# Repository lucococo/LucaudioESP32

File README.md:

View this project on [CADLAB.io](https://cadlab.io/project/28745). 

# LucaudioESP32

_Project inspired by [sonocotta ESP audio docks.](https://github.com/sonocotta/esp32-audio-dock/tree/main)_

I wanted a solution for wireless audio multiroom synchronized players, and the best I found was projects using [squeezelite-esp32](https://github.com/sle118/squeezelite-esp32).

I did my own board because firstly I wanted to improve my cad skills, and also because I like bringing my own personnal touch.
Project is still in development, I'm adding new features on my pcb later on

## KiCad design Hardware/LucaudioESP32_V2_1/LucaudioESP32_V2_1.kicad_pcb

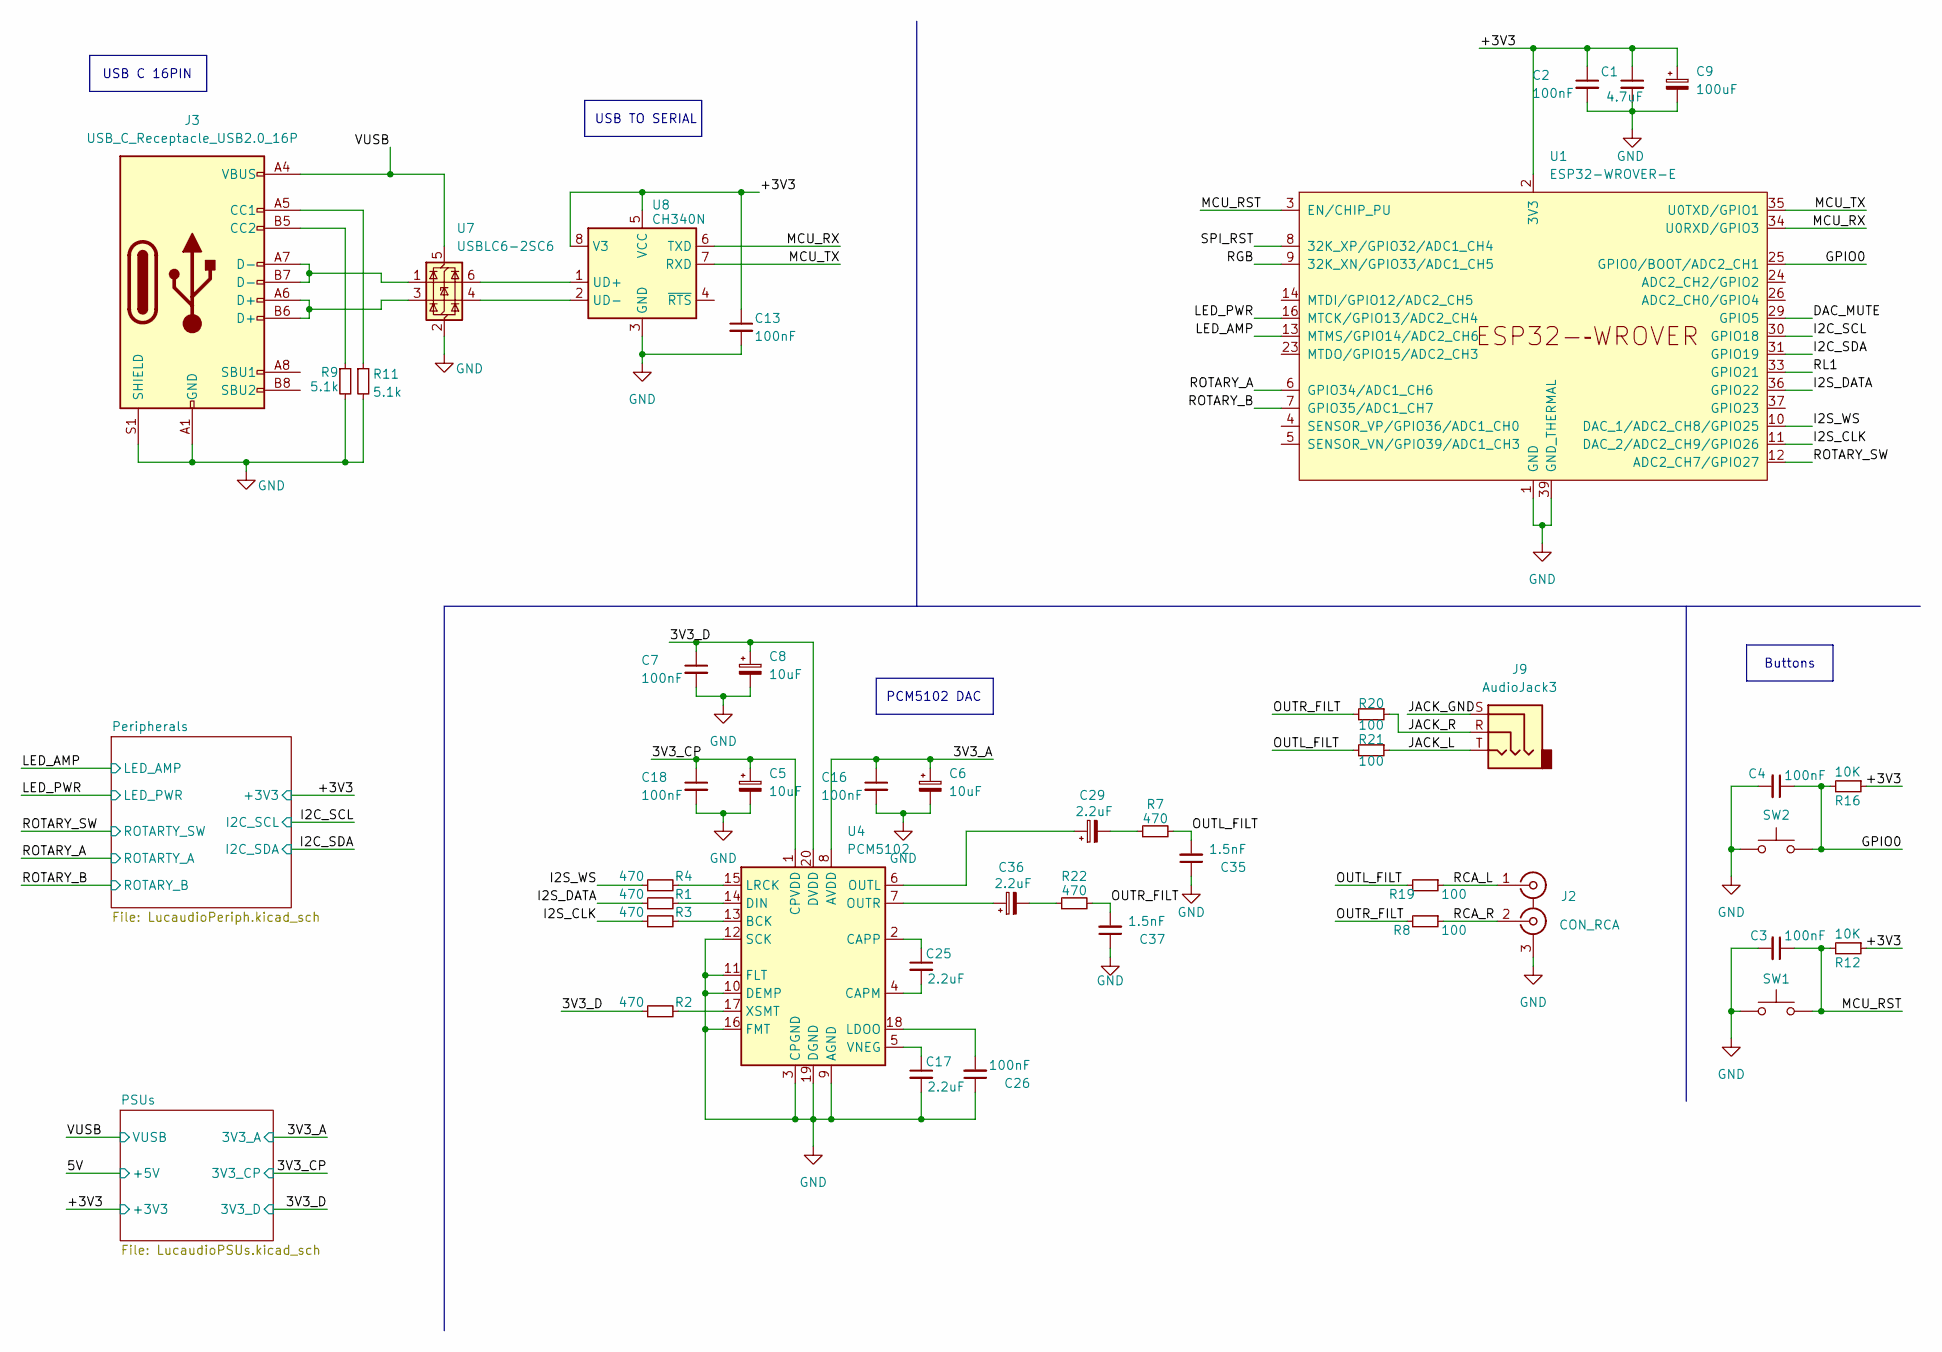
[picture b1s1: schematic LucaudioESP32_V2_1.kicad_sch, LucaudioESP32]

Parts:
C1: 4.7uF; C_0805_2012Metric_Pad1.18x1.45mm_HandSolder
C2, C7, C16, C18, C26: 100nF; C_0805_2012Metric_Pad1.18x1.45mm_HandSolder
C3, C4, C13: 100nF; C_0805_2012Metric
C5, C6, C8: 10uF; CP_Elec_5x4.5
C9: 100uF; CP_Elec_5x4.5
C17, C25: 2.2uF; C_0805_2012Metric_Pad1.18x1.45mm_HandSolder
C29, C36: 2.2uF; CP_EIA-3216-10_Kemet-I
C35, C37: 1.5nF; C_0805_2012Metric_Pad1.18x1.45mm_HandSolder
J2: CON_RCA; 2x RCA
J3: USB_C_Receptacle_USB2.0_16P; USB_C_Receptacle_G-Switch_GT-USB-7010ASV
J9: AudioJack3; JST_3p_audio
R1, R2, R3, R4, R7, R22: 470; R_0805_2012Metric_Pad1.20x1.40mm_HandSolder
R8, R19, R20, R21: 100; R_0805_2012Metric_Pad1.20x1.40mm_HandSolder
R9, R11: 5.1k; R_0805_2012Metric_Pad1.20x1.40mm_HandSolder
R12, R16: 10K; R_0805_2012Metric_Pad1.20x1.40mm_HandSolder
SW1, SW2: SW_Omron_B3FS; SW_SPST_Omron_B3FS-100xP
U1: ESP32-WROVER-E
U4: PCM5102; TSSOP-20_4.4x6.5mm_P0.65mm
U7: USBLC6-2SC6; SOT-23-6
U8: CH340N; SOP-8_3.9x4.9mm_P1.27mm

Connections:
/3V3_A: C6.1, C16.1, U4.8 (AVDD); also elsewhere on the board
/3V3_CP: C5.1, C18.1, U4.1 (CPVDD); also elsewhere on the board
/3V3_D: C7.1, C8.1, R2.1, U4.20 (DVDD); also elsewhere on the board
/+3V3: C1.1, C2.1, C9.1, C13.1, R12.1, R16.1, U1.2 (3V3), U8.5 (VCC), U8.8 (V3); also elsewhere on the board
/DAC_MUTE: U1.29 (GPIO5)
/GPIO0: C4.1, R16.2, SW2.2, U1.25 (GPIO0/BOOT/ADC2_CH1)
/I2C_SCL: U1.30 (GPIO18); also elsewhere on the board
/I2C_SDA: U1.31 (GPIO19); also elsewhere on the board
/I2S_CLK: R3.1, U1.11 (DAC_2/ADC2_CH9/GPIO26)
/I2S_DATA: R1.1, U1.36 (GPIO22)
/I2S_WS: R4.1, U1.10 (DAC_1/ADC2_CH8/GPIO25)
/JACK_GND: J9.S
/JACK_L: J9.T, R21.1
/JACK_R: J9.R, R20.1
/LED_AMP: U1.13 (MTMS/GPIO14/ADC2_CH6); also elsewhere on the board
/LED_PWR: U1.16 (MTCK/GPIO13/ADC2_CH4); also elsewhere on the board
/MCU_RST: C3.1, R12.2, SW1.2, U1.3 (EN/CHIP_PU)
/MCU_RX: U1.34 (U0RXD/GPIO3), U8.6 (TXD)
/MCU_TX: U1.35 (U0TXD/GPIO1), U8.7 (RXD)
/OUTL_FILT: C35.2, R7.2, R19.2, R21.2
/OUTR_FILT: C37.2, R8.2, R20.2, R22.2
/RCA_L: J2.1 (IN1), R19.1
/RCA_R: J2.2 (IN2), R8.1
/RGB: U1.9 (32K_XN/GPIO33/ADC1_CH5)
/RL1: U1.33 (GPIO21)
/ROTARY_A: U1.6 (GPIO34/ADC1_CH6); also elsewhere on the board
/ROTARY_B: U1.7 (GPIO35/ADC1_CH7); also elsewhere on the board
/ROTARY_SW: U1.12 (ADC2_CH7/GPIO27); also elsewhere on the board
/SPI_RST: U1.8 (32K_XP/GPIO32/ADC1_CH4)
/VUSB: J3.A4 (VBUS), J3.A9 (VBUS), J3.B4 (VBUS), J3.B9 (VBUS), U7.5 (VBUS); also elsewhere on the board
GND: C1.2, C2.2, C3.2, C4.2, C5.2, C6.2, C7.2, C8.2, C9.2, C13.2, C16.2, C17.2, C18.2, C26.1, C35.1, C37.1, J2.3 (EXT), J3.A1 (GND), J3.A12 (GND), J3.B1 (GND), J3.B12 (GND), J3.S1 (SHIELD), R9.2, R11.2, SW1.1, SW2.1, U1.1 (GND), U1.15 (GND), U1.38 (GND), U1.39 (GND_THERMAL), U4.3 (CPGND), U4.9 (AGND), U4.10 (DEMP), U4.11 (FLT), U4.12 (SCK), U4.16 (FMT), U4.19 (DGND), U7.2 (GND), U8.3 (GND); also elsewhere on the board
unnamed: C29.2, R7.1
unnamed: C36.2, R22.1
unnamed: J3.A5 (CC1), R11.1
unnamed: J3.B5 (CC2), R9.1
unnamed: J3.A6 (D+), J3.B6 (D+), U7.3 (I/O2)
unnamed: J3.A7 (D-), J3.B7 (D-), U7.1 (I/O1)
unnamed: R3.2, U4.13 (BCK)
unnamed: C25.2, U4.4 (CAPM)
unnamed: C25.1, U4.2 (CAPP)
unnamed: R1.2, U4.14 (DIN)
unnamed: C26.2, U4.18 (LDOO)
unnamed: R4.2, U4.15 (LRCK)
unnamed: C29.1, U4.6 (OUTL)
unnamed: C36.1, U4.7 (OUTR)
unnamed: C17.1, U4.5 (VNEG)
unnamed: R2.2, U4.17 (XSMT)
unnamed: U7.6 (I/O1), U8.1 (UD+)
unnamed: U7.4 (I/O2), U8.2 (UD-)

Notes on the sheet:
PCM5102 DAC
USB C 16PIN
Buttons
USB TO SERIAL

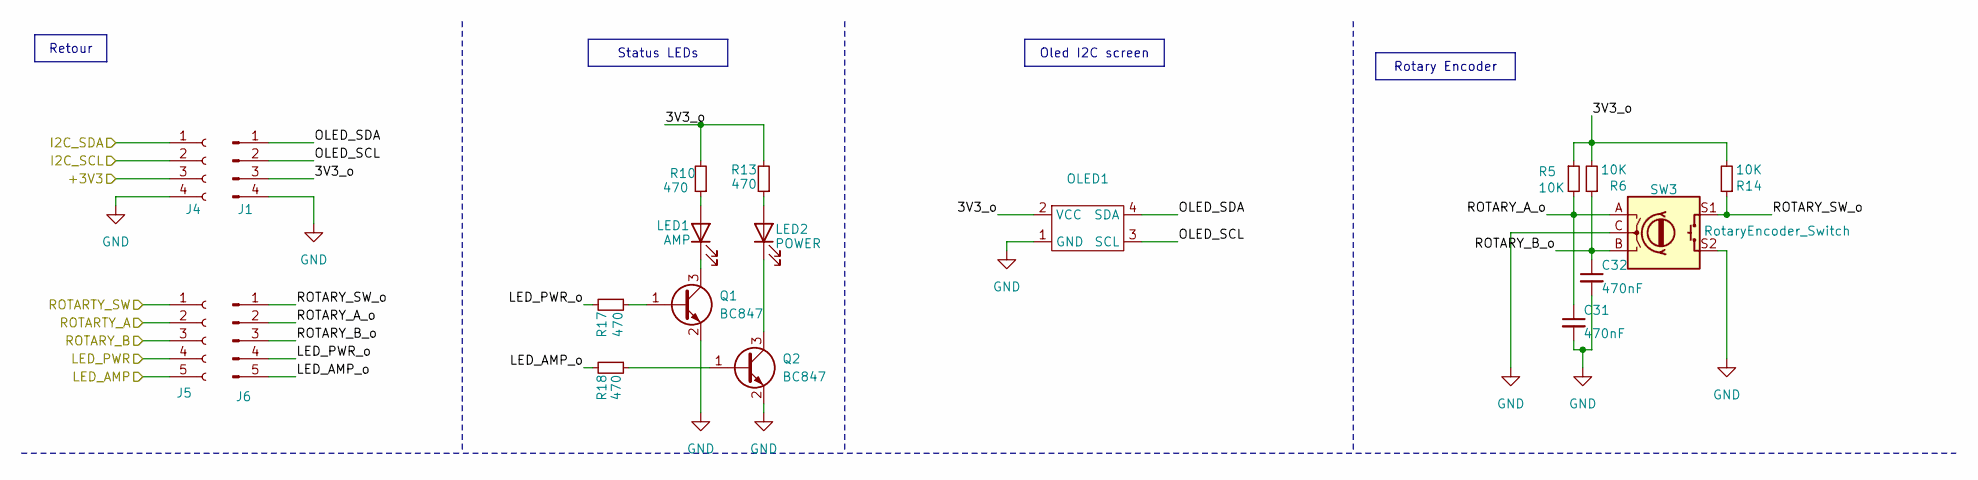
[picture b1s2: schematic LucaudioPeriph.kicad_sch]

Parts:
C31, C32: 470nF; C_0805_2012Metric_Pad1.18x1.45mm_HandSolder
J1: Conn_01x04_Pin; PinHeader_1x04_P2.54mm_Horizontal
J4: Conn_01x04_Socket; PinSocket_1x04_P2.54mm_Vertical
J5: Conn_01x05_Socket; PinSocket_1x05_P2.54mm_Vertical
J6: Conn_01x05_Pin; PinHeader_1x05_P2.54mm_Horizontal
LED1: AMP; LED_0805_2012Metric_Pad1.15x1.40mm_HandSolder
LED2: POWER; LED_0805_2012Metric_Pad1.15x1.40mm_HandSolder
OLED1: OLED_128_32
Q1, Q2: BC847; SOT-23
R5, R6, R14: 10K; R_0805_2012Metric_Pad1.20x1.40mm_HandSolder
R10, R13, R17, R18: 470; R_0805_2012Metric_Pad1.20x1.40mm_HandSolder
SW3: RotaryEncoder_Switch; RotaryEncoder_Alps_EC11E-Switch_Vertical_H20mm

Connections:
/+3V3: J4.3; also elsewhere on the board
/I2C_SCL: J4.2; also elsewhere on the board
/I2C_SDA: J4.1; also elsewhere on the board
/LED_AMP: J5.5; also elsewhere on the board
/LED_PWR: J5.4; also elsewhere on the board
/Peripherals/3V3_o: J1.3, OLED1.2 (VCC), R5.1, R6.2, R10.2, R13.2, R14.2
/Peripherals/LED_AMP_o: J6.5, R18.2
/Peripherals/LED_PWR_o: J6.4, R17.2
/Peripherals/OLED_SCL: J1.2, OLED1.3 (SCL)
/Peripherals/OLED_SDA: J1.1, OLED1.4 (SDA)
/Peripherals/ROTARY_A_o: C31.1, J6.2, R5.2, SW3.A
/Peripherals/ROTARY_B_o: C32.1, J6.3, R6.1, SW3.B
/Peripherals/ROTARY_SW_o: J6.1, R14.1, SW3.S1
/ROTARY_A: J5.2; also elsewhere on the board
/ROTARY_B: J5.3; also elsewhere on the board
/ROTARY_SW: J5.1; also elsewhere on the board
GND: C31.2, C32.2, J1.4, J4.4, OLED1.1 (GND), Q1.2 (E), Q2.2 (E), SW3.C, SW3.S2; also elsewhere on the board
unnamed: LED1.2 (A), R10.1
unnamed: LED1.1 (K), Q1.3 (C)
unnamed: LED2.2 (A), R13.1
unnamed: LED2.1 (K), Q2.3 (C)
unnamed: Q1.1 (B), R17.1
unnamed: Q2.1 (B), R18.1

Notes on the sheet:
Oled I2C screen
Rotary Encoder
Retour
Status LEDs

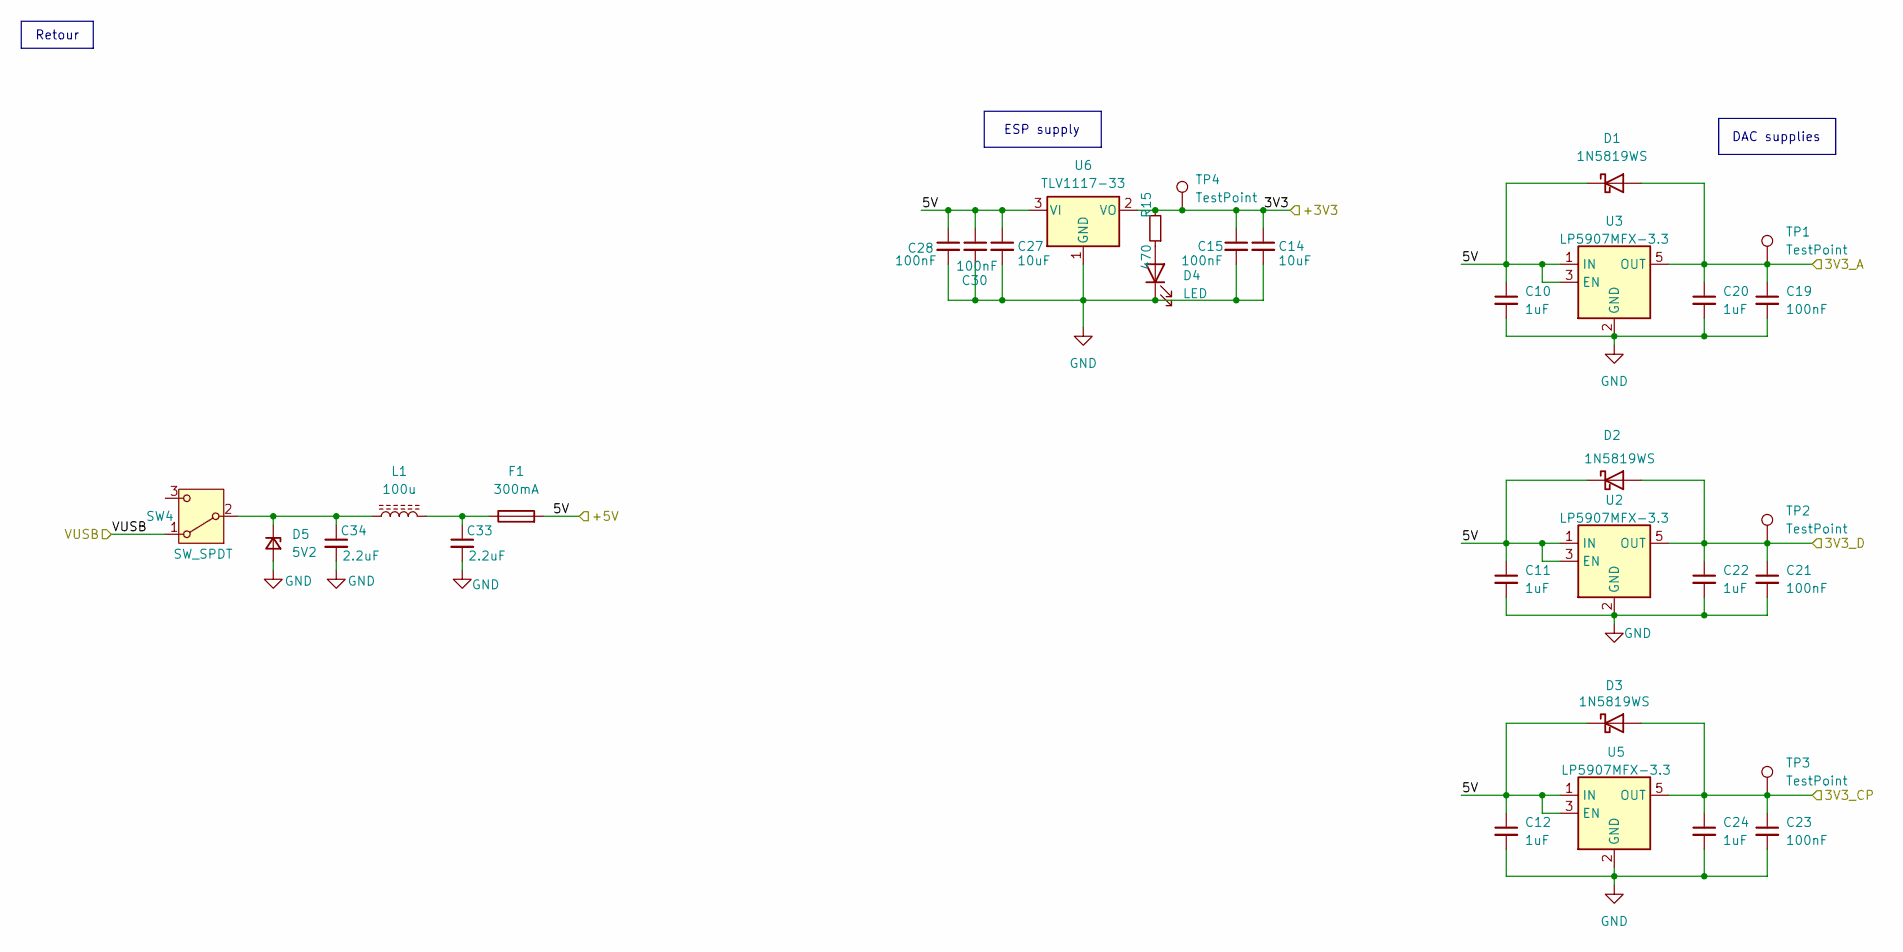
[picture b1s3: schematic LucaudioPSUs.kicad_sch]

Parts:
C10, C11, C12, C20, C22, C24: 1uF; C_0805_2012Metric
C14, C27: 10uF; C_0805_2012Metric
C15, C19, C21, C23, C28, C30: 100nF; C_0805_2012Metric
C33, C34: 2.2uF; C_0805_2012Metric_Pad1.18x1.45mm_HandSolder
D1, D2, D3: 1N5819WS; D_SOD-323_HandSoldering
D4: LED; LED_0805_2012Metric_Pad1.15x1.40mm_HandSolder
D5: 5V2; D_SMA
F1: 300mA; Fuse_0805_2012Metric
L1: 100u; L_Sunlord_SWPA4018S
R15: 470; R_0805_2012Metric_Pad1.20x1.40mm_HandSolder
SW4: SW_SPDT; Slide_angular_SPDT
TP1, TP2, TP3, TP4: TestPoint; TestPoint_Pad_1.0x1.0mm
U2, U3, U5: LP5907MFX-3.3; SOT-23-5
U6: TLV1117-33; SOT-223-3_TabPin2

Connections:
/3V3_A: C19.1, C20.1, D1.2 (A), TP1.1, U3.5 (OUT); also elsewhere on the board
/3V3_CP: C23.1, C24.1, D3.2 (A), TP3.1, U5.5 (OUT); also elsewhere on the board
/3V3_D: C21.1, C22.1, D2.2 (A), TP2.1, U2.5 (OUT); also elsewhere on the board
/5V: C10.1, C11.1, C12.1, C27.1, C28.1, C30.1, D1.1 (K), D2.1 (K), D3.1 (K), F1.2, U2.1 (IN), U2.3 (EN), U3.1 (IN), U3.3 (EN), U5.1 (IN), U5.3 (EN), U6.3 (VI)
/+3V3: C14.1, C15.1, R15.2, TP4.1, U6.2 (VO); also elsewhere on the board
/VUSB: SW4.1 (A); also elsewhere on the board
GND: C10.2, C11.2, C12.2, C14.2, C15.2, C19.2, C20.2, C21.2, C22.2, C23.2, C24.2, C27.2, C28.2, C30.2, C33.2, C34.2, D4.1 (K), D5.2 (A), U2.2 (GND), U3.2 (GND), U5.2 (GND), U6.1 (GND); also elsewhere on the board
unnamed: C33.1, F1.1, L1.2
unnamed: D4.2 (A), R15.1
unnamed: C34.1, D5.1 (K), L1.1, SW4.2 (B)

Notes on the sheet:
ESP supply
DAC supplies
Retour

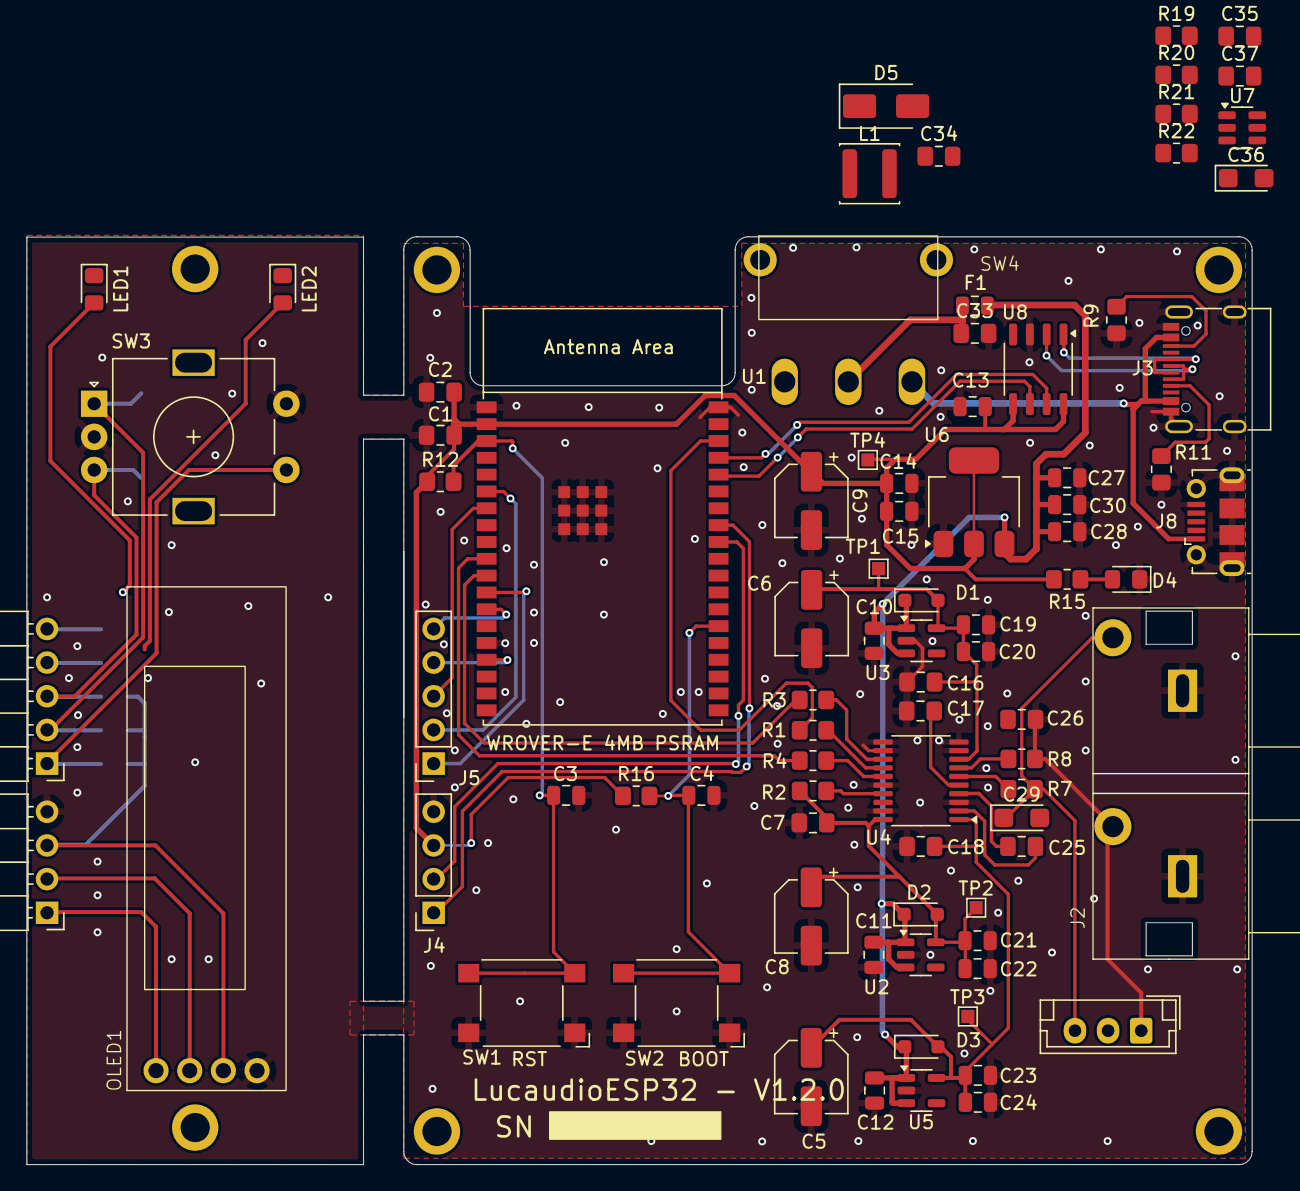
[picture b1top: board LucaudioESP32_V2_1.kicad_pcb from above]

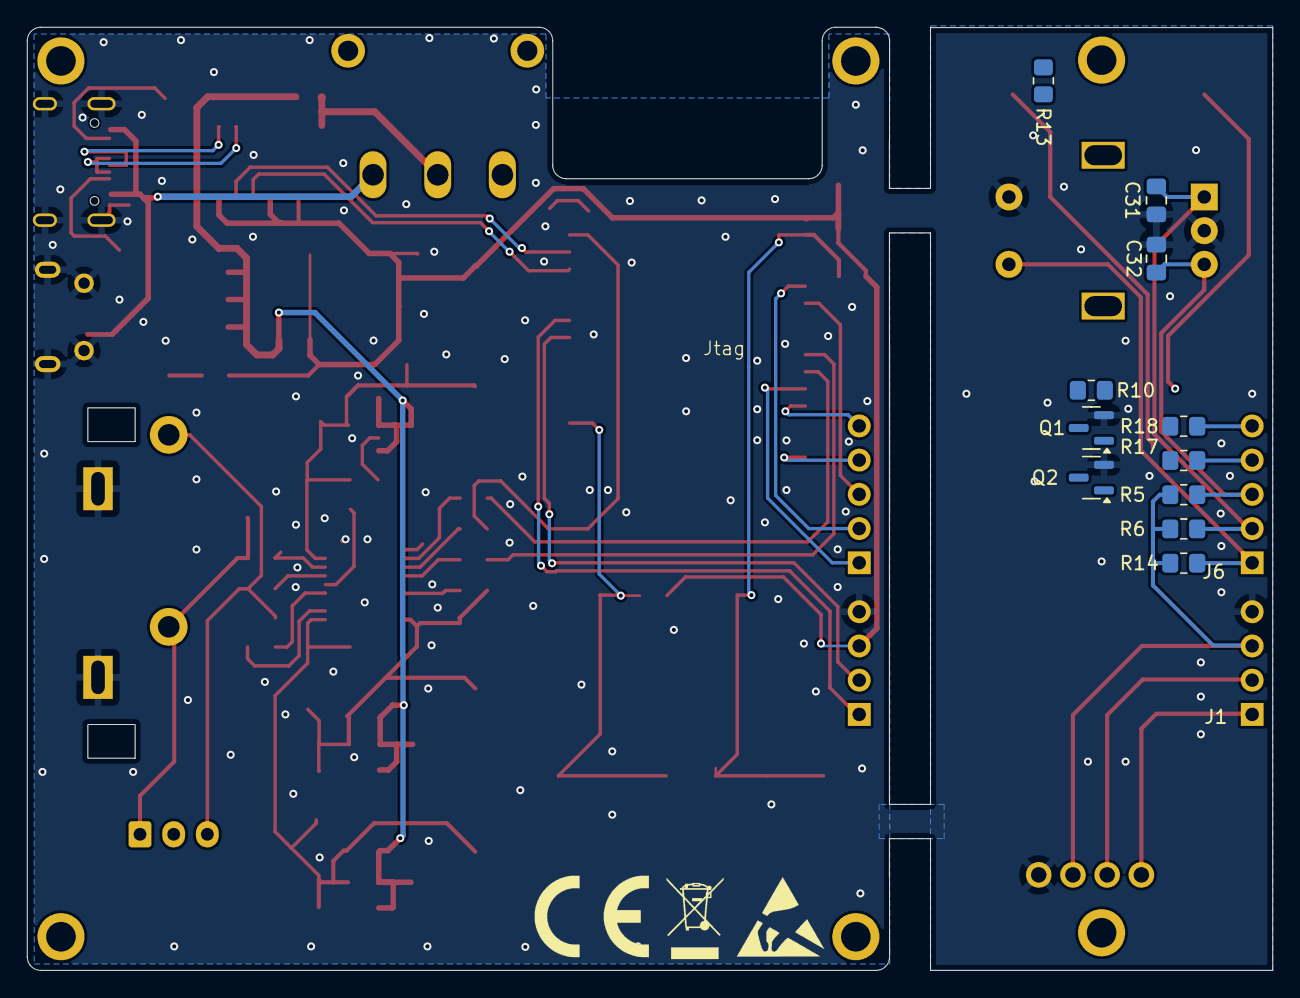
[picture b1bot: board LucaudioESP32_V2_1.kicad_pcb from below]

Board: 2 copper layers, 92.4 x 70.0 mm, 95 parts (11 on the bottom side), 62 nets.

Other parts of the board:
J8: USB_B_Micro; USB_Micro-B_Molex-105017-0001

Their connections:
GND: J8.5 (GND), J8.6 (Shield); also elsewhere on the board

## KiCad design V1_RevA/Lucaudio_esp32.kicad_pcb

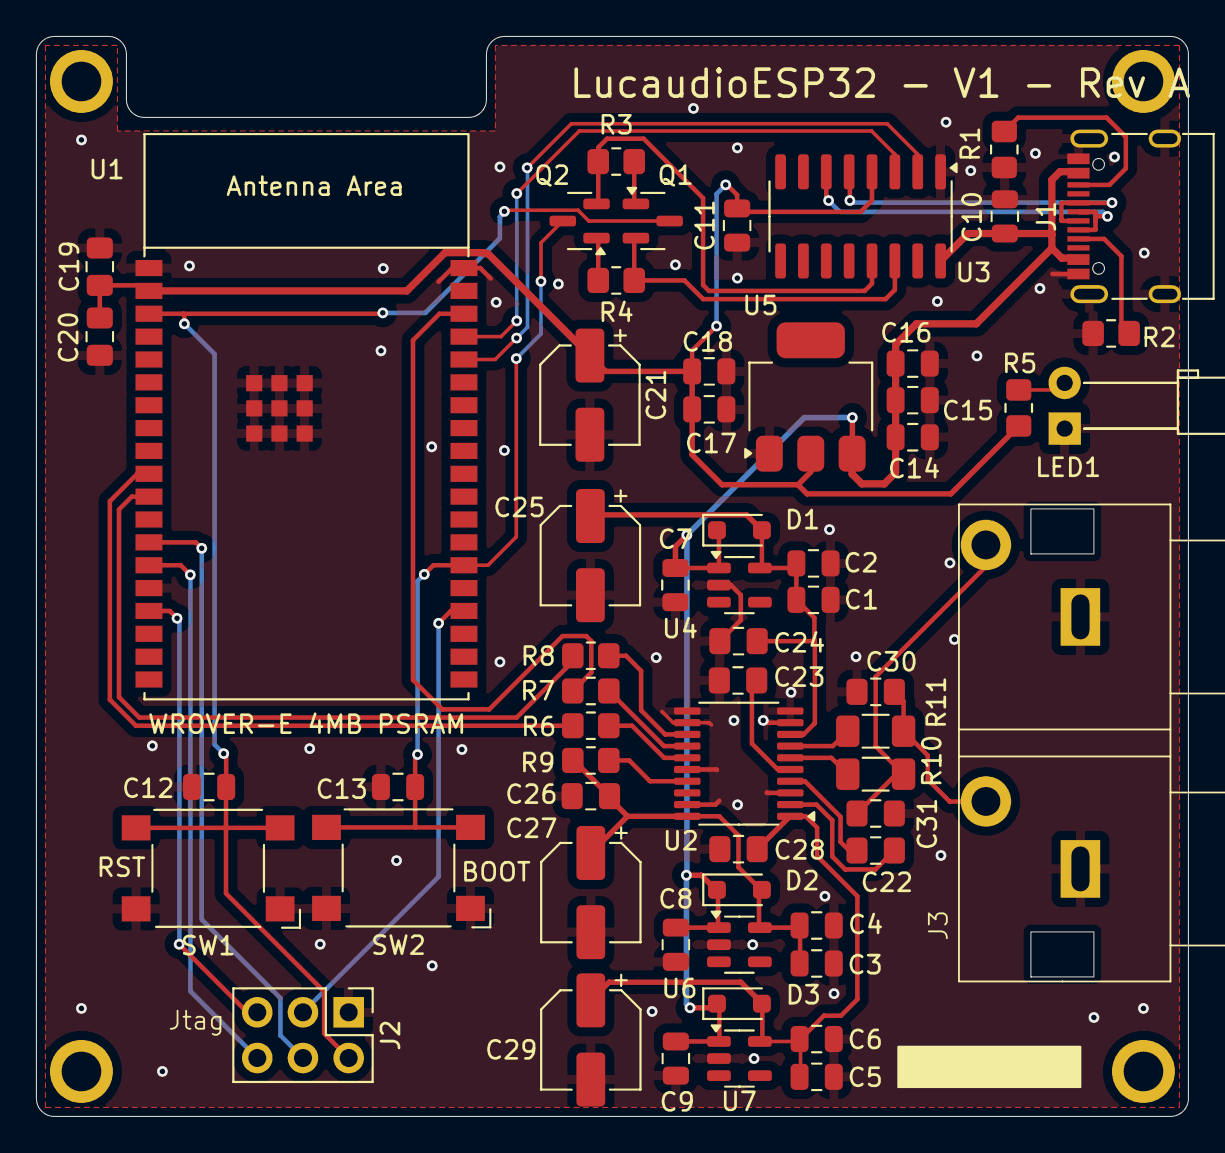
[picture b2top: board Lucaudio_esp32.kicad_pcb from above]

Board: 2 copper layers, 64.0 x 60.0 mm, 60 parts (0 on the bottom side), 37 nets.

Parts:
C1, C3, C5, C7, C8, C9: 1uF; C_0805_2012Metric
C2, C4, C6, C10, C11, C12, C13, C14, C15, C17: 100nF; C_0805_2012Metric
C16, C18: 10uF; C_0805_2012Metric
C19, C24, C26, C28: 100nF; C_0805_2012Metric_Pad1.18x1.45mm_HandSolder
C20: 4.7uF; C_0805_2012Metric_Pad1.18x1.45mm_HandSolder
C21: 100uF; CP_Elec_5x4.5
C22, C23: 2.2uF; C_0805_2012Metric_Pad1.18x1.45mm_HandSolder
C25, C27, C29: 10uF; CP_Elec_5x4.5
C30, C31: 2.2nF; C_0805_2012Metric_Pad1.18x1.45mm_HandSolder
D1, D2, D3: 1N5819WS; D_SOD-323_HandSoldering
J1: USB_C_Receptacle_USB2.0_16P; USB_C_Receptacle_G-Switch_GT-USB-7010ASV
J2: jtag; PinHeader_2x03_P2.54mm_Vertical
J3: Conn_Coaxial_x2; 2x RCA
LED1: RED; LED_D3.0mm_Horizontal_O6.35mm_Z10.0mm
Q1, Q2: BC847; SOT-23
R1, R2: 5.1k; R_0805_2012Metric_Pad1.20x1.40mm_HandSolder
R3, R4: 10K; R_0805_2012Metric_Pad1.20x1.40mm_HandSolder
R5: 1K; R_0805_2012Metric_Pad1.20x1.40mm_HandSolder
R6, R7, R8, R9: 470; R_0805_2012Metric_Pad1.20x1.40mm_HandSolder
R10, R11: 470; R_1206_3216Metric_Pad1.30x1.75mm_HandSolder
SW1, SW2: SW_Omron_B3FS; SW_SPST_Omron_B3FS-100xP
U1: ESP32-WROVER-E
U2: PCM5100; TSSOP-20_4.4x6.5mm_P0.65mm
U3: CH340C; SOIC-16_3.9x9.9mm_P1.27mm
U4, U6, U7: LP5907MFX-3.3; SOT-23-5
U5: TLV1117-33; SOT-223-3_TabPin2

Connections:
3V3: C11.1, C17.1, C18.1, C19.1, C20.1, C21.1, R5.1, U1.2 (3V3), U3.4 (V3), U5.2 (VO)
3V3_1: C1.1, C2.1, C24.1, C25.1, D1.2 (A), U2.8 (AVDD), U4.5 (OUT)
3V3_2: C3.1, C4.1, C26.1, C27.1, D2.2 (A), R9.1, U2.20 (DVDD), U6.5 (OUT)
3V3_3: C5.1, C6.1, C28.1, C29.1, D3.2 (A), U2.1 (CPVDD), U7.5 (OUT)
+5V: C7.1, C8.1, C9.1, C10.1, C14.1, C15.1, C16.1, D1.1 (K), D2.1 (K), D3.1 (K), J1.A4 (VBUS), J1.A9 (VBUS), J1.B4 (VBUS), J1.B9 (VBUS), U3.16 (VCC), U4.1 (IN), U5.3 (VI), U6.1 (IN), U7.1 (IN)
DTR: Q2.2 (E), R3.1, U3.13 (~DTR)
GND: C1.2, C2.2, C3.2, C4.2, C5.2, C6.2, C7.2, C8.2, C9.2, C10.2, C11.2, C12.2, C13.2, C14.2, C15.2, C16.2, C17.2, C18.2, C19.2, C20.2, C21.2, C23.2, C24.2, C25.2, C26.2, C27.2, C28.2, C29.2, C30.2, C31.2, J1.A1 (GND), J1.A12 (GND), J1.B1 (GND), J1.B12 (GND), J1.S1 (SHIELD), J2.1, J3.3 (EXT), LED1.1 (K), R1.2, R2.2, SW1.1, SW2.1, U1.1 (GND), U1.15 (GND), U1.38 (GND), U1.39 (GND_THERMAL), U2.3 (CPGND), U2.9 (AGND), U2.10 (DEMP), U2.11 (FLT), U2.12 (SCK), U2.16 (FMT), U2.19 (DGND), U3.1 (GND), U4.2 (GND), U5.1 (GND), U6.2 (GND), U7.2 (GND)
GPIO0: C13.1, Q2.3 (C), SW2.2, U1.25 (GPIO0/BOOT/ADC2_CH1)
GPIO12: J2.6, U1.14 (MTDI/GPIO12/ADC2_CH5)
GPIO13: J2.5, U1.16 (MTCK/GPIO13/ADC2_CH4)
GPIO14: J2.4, U1.13 (MTMS/GPIO14/ADC2_CH6)
GPIO15: J2.3, U1.23 (MTDO/GPIO15/ADC2_CH3)
I2S_CLK: R8.1, U1.11 (DAC_2/ADC2_CH9/GPIO26)
I2S_DATA: R7.1, U1.36 (GPIO22)
I2S_WS: R6.1, U1.10 (DAC_1/ADC2_CH8/GPIO25)
MCU_RST: C12.1, J2.2, Q1.3 (C), SW1.2, U1.3 (EN/CHIP_PU)
MCU_RX: U1.34 (U0RXD/GPIO3), U3.2 (TXD)
MCU_TX: U1.35 (U0TXD/GPIO1), U3.3 (RXD)
unnamed: J1.A5 (CC1), R2.1
unnamed: J1.B5 (CC2), R1.1
unnamed: C31.1, J3.1 (IN1), R10.2
unnamed: C30.1, J3.2 (IN2), R11.2
unnamed: LED1.2 (A), R5.2
unnamed: Q1.1 (B), R3.2
unnamed: Q2.1 (B), R4.2
unnamed: R8.2, U2.13 (BCK)
unnamed: C22.2, U2.4 (CAPM)
unnamed: C22.1, U2.2 (CAPP)
unnamed: R7.2, U2.14 (DIN)
unnamed: R6.2, U2.15 (LRCK)
unnamed: R10.1, U2.6 (OUTL)
unnamed: R11.1, U2.7 (OUTR)
unnamed: C23.1, U2.5 (VNEG)
unnamed: R9.2, U2.17 (XSMT)
unnamed: J1.A6 (D+), J1.B6 (D+), U3.5 (UD+)
unnamed: J1.A7 (D-), J1.B7 (D-), U3.6 (UD-)
RTS: Q1.2 (E), R4.1, U3.14 (~RTS)

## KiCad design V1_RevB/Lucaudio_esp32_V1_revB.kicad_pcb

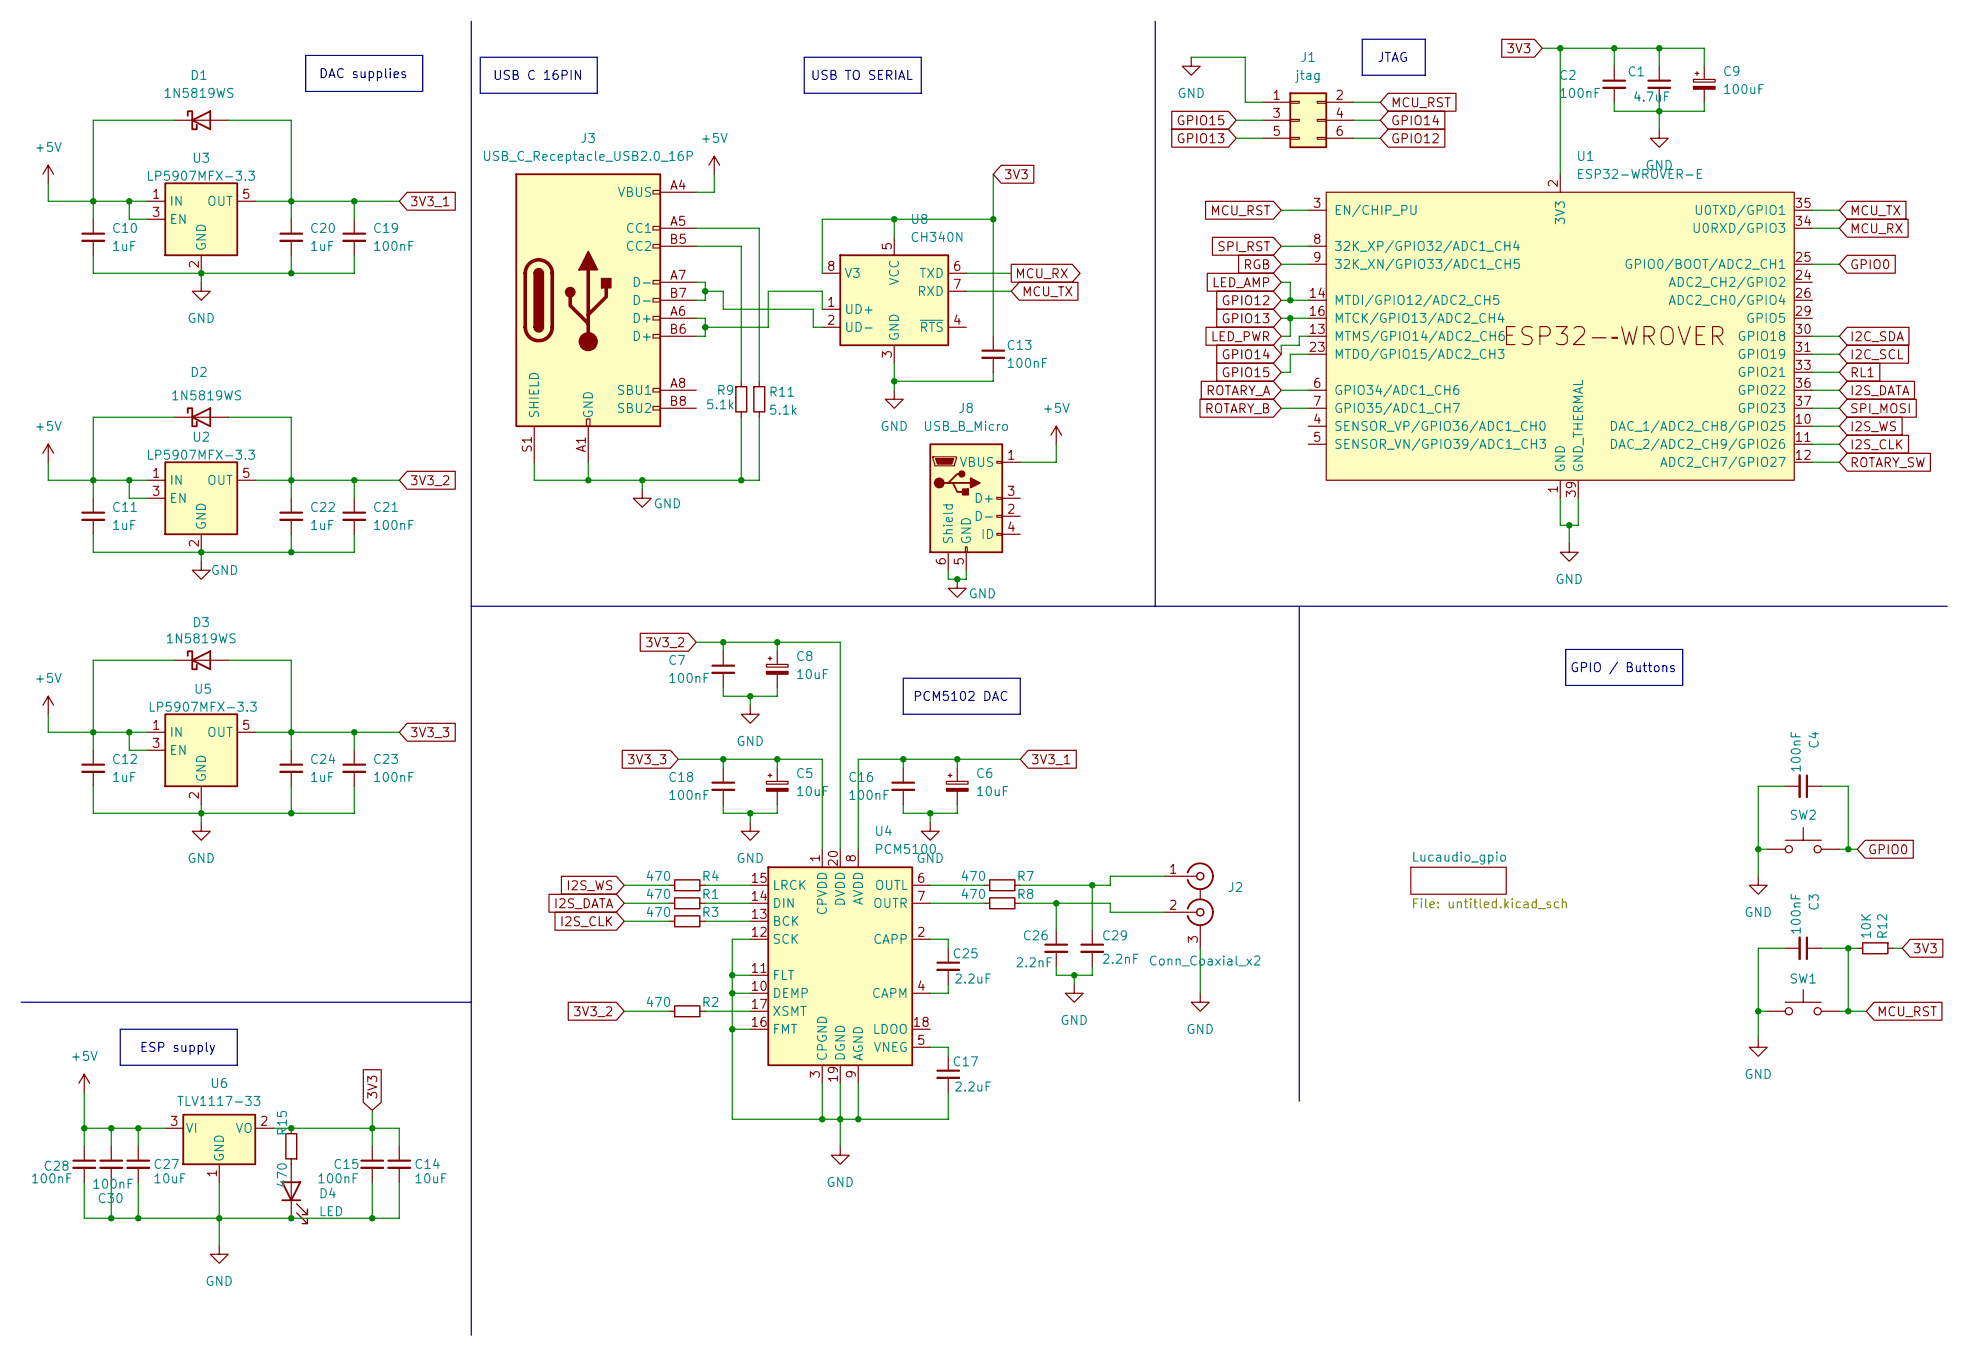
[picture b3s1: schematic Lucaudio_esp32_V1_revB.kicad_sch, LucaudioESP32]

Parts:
C1: 4.7uF; C_0805_2012Metric_Pad1.18x1.45mm_HandSolder
C2, C7, C16, C18: 100nF; C_0805_2012Metric_Pad1.18x1.45mm_HandSolder
C3, C4, C13, C15, C19, C21, C23, C28, C30: 100nF; C_0805_2012Metric
C5, C6, C8: 10uF; CP_Elec_5x4.5
C9: 100uF; CP_Elec_5x4.5
C10, C11, C12, C20, C22, C24: 1uF; C_0805_2012Metric
C14, C27: 10uF; C_0805_2012Metric
C17, C25: 2.2uF; C_0805_2012Metric_Pad1.18x1.45mm_HandSolder
C26, C29: 2.2nF; C_0805_2012Metric_Pad1.18x1.45mm_HandSolder
D1, D2, D3: 1N5819WS; D_SOD-323_HandSoldering
D4: LED; LED_0805_2012Metric_Pad1.15x1.40mm_HandSolder
J1: jtag; PinHeader_2x03_P2.54mm_Vertical
J2: Conn_Coaxial_x2; 2x RCA
J3: USB_C_Receptacle_USB2.0_16P; USB_C_Receptacle_G-Switch_GT-USB-7010ASV
J8: USB_B_Micro; USB_Micro-B_Molex-105017-0001
R1, R2, R3, R4, R15: 470; R_0805_2012Metric_Pad1.20x1.40mm_HandSolder
R7, R8: 470; R_1206_3216Metric_Pad1.30x1.75mm_HandSolder
R9, R11: 5.1k; R_0805_2012Metric_Pad1.20x1.40mm_HandSolder
R12: 10K; R_0805_2012Metric_Pad1.20x1.40mm_HandSolder
SW1, SW2: SW_Omron_B3FS; SW_SPST_Omron_B3FS-100xP
U1: ESP32-WROVER-E
U2, U3, U5: LP5907MFX-3.3; SOT-23-5
U4: PCM5100; TSSOP-20_4.4x6.5mm_P0.65mm
U6: TLV1117-33; SOT-223-3_TabPin2
U8: CH340N; SOP-8_3.9x4.9mm_P1.27mm

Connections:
3V3: C1.1, C2.1, C9.1, C13.1, C14.1, C15.1, R12.1, R15.2, U1.2 (3V3), U6.2 (VO), U8.5 (VCC), U8.8 (V3); also elsewhere on the board
3V3_1: C6.1, C16.1, C19.1, C20.1, D1.2 (A), U3.5 (OUT), U4.8 (AVDD)
3V3_2: C7.1, C8.1, C21.1, C22.1, D2.2 (A), R2.1, U2.5 (OUT), U4.20 (DVDD)
3V3_3: C5.1, C18.1, C23.1, C24.1, D3.2 (A), U4.1 (CPVDD), U5.5 (OUT)
+5V: C10.1, C11.1, C12.1, C27.1, C28.1, C30.1, D1.1 (K), D2.1 (K), D3.1 (K), J3.A4 (VBUS), J3.A9 (VBUS), J3.B4 (VBUS), J3.B9 (VBUS), J8.1 (VBUS), U2.1 (IN), U2.3 (EN), U3.1 (IN), U3.3 (EN), U5.1 (IN), U5.3 (EN), U6.3 (VI); also elsewhere on the board
GND: C1.2, C2.2, C3.2, C4.2, C5.2, C6.2, C7.2, C8.2, C9.2, C10.2, C11.2, C12.2, C13.2, C14.2, C15.2, C16.2, C17.2, C18.2, C19.2, C20.2, C21.2, C22.2, C23.2, C24.2, C26.2, C27.2, C28.2, C29.2, C30.2, D4.1 (K), J1.1, J2.3 (EXT), J3.A1 (GND), J3.A12 (GND), J3.B1 (GND), J3.B12 (GND), J3.S1 (SHIELD), J8.5 (GND), J8.6 (Shield), R9.2, R11.2, SW1.1, SW2.1, U1.1 (GND), U1.15 (GND), U1.38 (GND), U1.39 (GND_THERMAL), U2.2 (GND), U3.2 (GND), U4.3 (CPGND), U4.9 (AGND), U4.10 (DEMP), U4.11 (FLT), U4.12 (SCK), U4.16 (FMT), U4.19 (DGND), U5.2 (GND), U6.1 (GND), U8.3 (GND); also elsewhere on the board
GPIO0: C4.1, SW2.2, U1.25 (GPIO0/BOOT/ADC2_CH1)
GPIO12: J1.6, U1.14 (MTDI/GPIO12/ADC2_CH5); also elsewhere on the board
GPIO13: J1.5, U1.16 (MTCK/GPIO13/ADC2_CH4); also elsewhere on the board
GPIO14: J1.4, U1.13 (MTMS/GPIO14/ADC2_CH6)
GPIO15: J1.3, U1.23 (MTDO/GPIO15/ADC2_CH3)
I2C_SCL: U1.31 (GPIO19); also elsewhere on the board
I2C_SDA: U1.30 (GPIO18); also elsewhere on the board
I2S_CLK: R3.1, U1.11 (DAC_2/ADC2_CH9/GPIO26)
I2S_DATA: R1.1, U1.36 (GPIO22)
I2S_WS: R4.1, U1.10 (DAC_1/ADC2_CH8/GPIO25)
MCU_RST: C3.1, J1.2, R12.2, SW1.2, U1.3 (EN/CHIP_PU)
MCU_RX: U1.34 (U0RXD/GPIO3), U8.6 (TXD)
MCU_TX: U1.35 (U0TXD/GPIO1), U8.7 (RXD)
unnamed: D4.2 (A), R15.1
unnamed: C29.1, J2.1 (IN1), R7.2
unnamed: C26.1, J2.2 (IN2), R8.2
unnamed: J3.A5 (CC1), R11.1
unnamed: J3.B5 (CC2), R9.1
unnamed: R3.2, U4.13 (BCK)
unnamed: C25.2, U4.4 (CAPM)
unnamed: C25.1, U4.2 (CAPP)
unnamed: R1.2, U4.14 (DIN)
unnamed: R4.2, U4.15 (LRCK)
unnamed: R7.1, U4.6 (OUTL)
unnamed: R8.1, U4.7 (OUTR)
unnamed: C17.1, U4.5 (VNEG)
unnamed: R2.2, U4.17 (XSMT)
unnamed: J3.A6 (D+), J3.B6 (D+), U8.1 (UD+)
unnamed: J3.A7 (D-), J3.B7 (D-), U8.2 (UD-)
RGB: U1.9 (32K_XN/GPIO33/ADC1_CH5)
RL1: U1.33 (GPIO21)
ROTARY_A: U1.6 (GPIO34/ADC1_CH6); also elsewhere on the board
ROTARY_B: U1.7 (GPIO35/ADC1_CH7); also elsewhere on the board
ROTARY_SW: U1.12 (ADC2_CH7/GPIO27); also elsewhere on the board
SPI_MOSI: U1.37 (GPIO23)
SPI_RST: U1.8 (32K_XP/GPIO32/ADC1_CH4)

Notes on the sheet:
PCM5102 DAC
USB C 16PIN
DAC supplies
GPIO / Buttons
JTAG
ESP supply
USB TO SERIAL
